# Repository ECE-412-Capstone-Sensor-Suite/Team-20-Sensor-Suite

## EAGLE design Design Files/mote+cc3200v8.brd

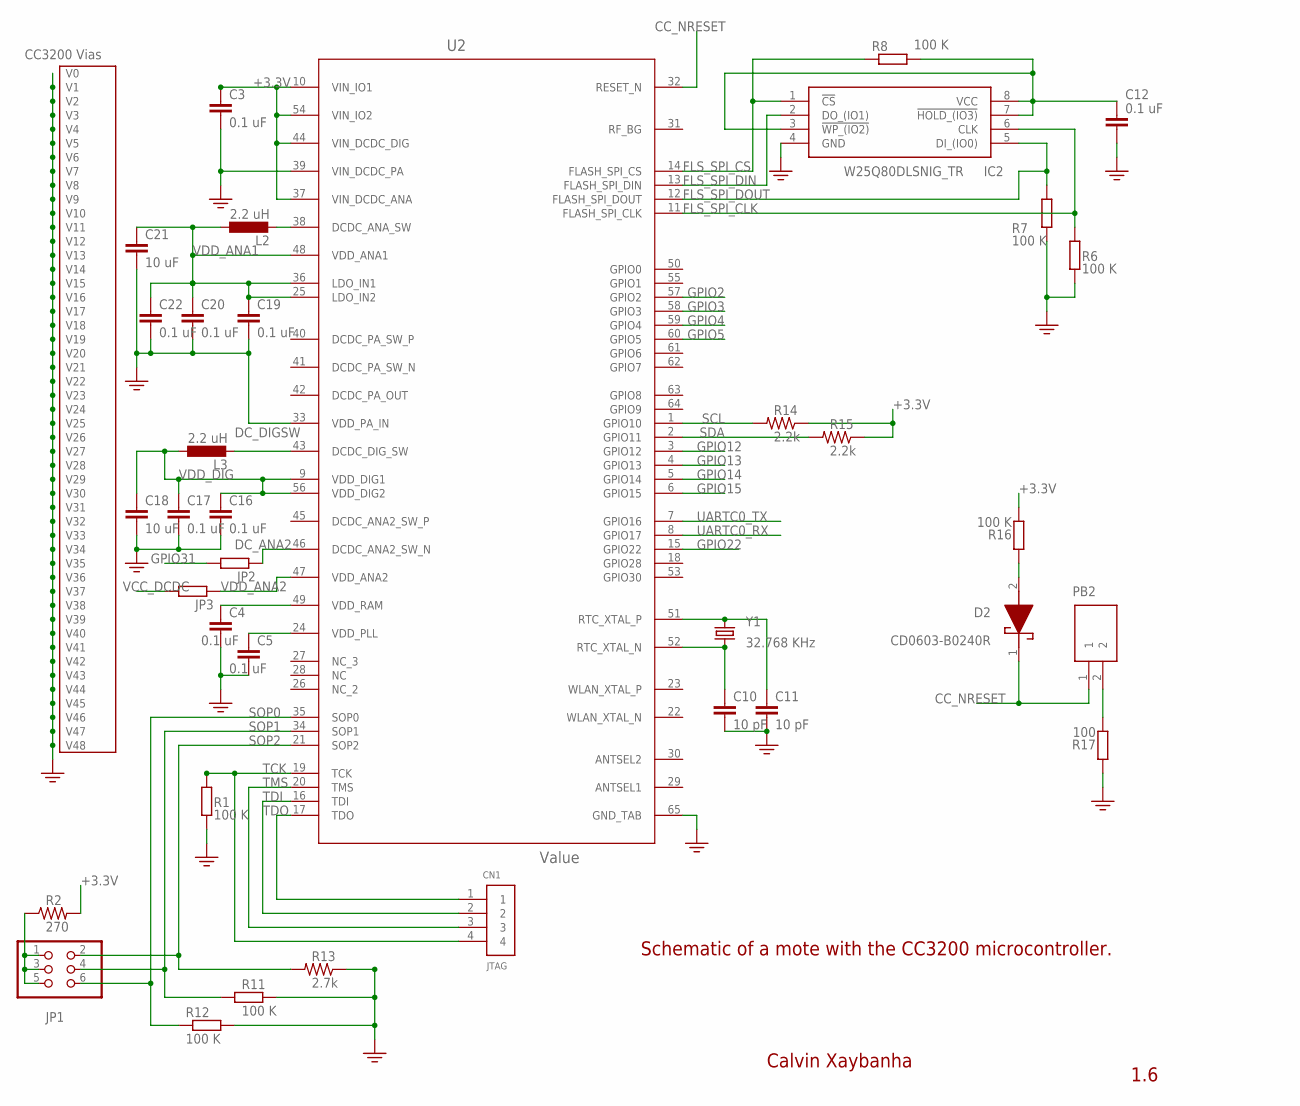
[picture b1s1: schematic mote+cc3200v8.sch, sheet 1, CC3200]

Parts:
C3, C4, C5, C12, C16, C17, C19, C20, C22: 0.1 uF; C1808
C10, C11: 10 pF; C1808
C18, C21: 10 uF; C1808
CN1: JTAG; 1X04-BIG
D2: CD0603-B0240R; CD0603B0240R
IC2: W25Q80DLSNIG_TR; SOIC127P600X175-8N
JP1: PINHD-2X3/90; 2X03/90
JP2, JP3: RR0201; R0201
L2, L3: 2.2 uH; L3216C
PB2: FSMSM
R1, R6, R7, R8, R11, R12, R16: 100 K; R1206
R2: 270; RES_1206
R13: 2.7k; RES_1206
R14, R15: 2.2k; RES_1206
R17: 100; R1206
U2: Value; RGC0064A
Y1: 32.768 KHz; 7.0X5.0

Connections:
+3.3V: C3.1, C12.1, IC2.3 (!WP_(IO2)), IC2.7 (!HOLD_(IO3)), IC2.8 (VCC), R2.2, R8.2, R14.1, R15.1, R16.2, U2.10 (VIN_IO1), U2.37 (VIN_DCDC_ANA), U2.44 (VIN_DCDC_DIG), U2.54 (VIN_IO2); also elsewhere on the board
CC_NRESET: D2.1 (K), PB2.1, U2.32 (RESET_N)
D2_P2: D2.2 (A), R16.1
DCDC_PA_OUT: U2.42 (DCDC_PA_OUT)
DCDC_PA_SW_N: U2.41 (DCDC_PA_SW_N)
DCDC_PA_SW_P: U2.40 (DCDC_PA_SW_P)
DC_ANA2: JP2.1, U2.46 (DCDC_ANA2_SW_N)
DC_DIGSW: L3.2, U2.43 (DCDC_DIG_SW)
FLS_SPI_CLK: IC2.6 (CLK), R6.1, U2.11 (FLASH_SPI_CLK)
FLS_SPI_CS: IC2.1 (!CS), R8.1, U2.14 (FLASH_SPI_CS)
FLS_SPI_DIN: IC2.2 (DO_(IO1)), U2.13 (FLASH_SPI_DIN)
FLS_SPI_DOUT: IC2.5 (DI_(IO0)), R7.1, U2.12 (FLASH_SPI_DOUT)
GND: C3.2, C4.2, C5.2, C10.2, C11.2, C12.2, C16.2, C17.2, C18.2, C19.2, C20.2, C21.2, C22.2, IC2.4 (GND), R1.2, R6.2, R7.2, R11.2, R12.2, R13.1, R17.1, U2.33 (VDD_PA_IN), U2.39 (VIN_DCDC_PA), U2.65 (GND_TAB), U2.V (V0), U2.V_1 (V1), U2.V_2 (V2), U2.V_3 (V3), U2.V_4 (V4), U2.V_5 (V5), U2.V_6 (V6), U2.V_7 (V7), U2.V_8 (V8), U2.V_9 (V9), U2.V_10 (V10), U2.V_11 (V11), U2.V_12 (V12), U2.V_13 (V13), U2.V_14 (V14), U2.V_15 (V15), U2.V_16 (V16), U2.V_17 (V17), U2.V_18 (V18), U2.V_19 (V19), U2.V_20 (V20), U2.V_21 (V21), U2.V_22 (V22), U2.V_23 (V23), U2.V_24 (V24), U2.V_25 (V25), U2.V_26 (V26), U2.V_27 (V27), U2.V_28 (V28), U2.V_29 (V29), U2.V_30 (V30), U2.V_31 (V31), U2.V_32 (V32), U2.V_33 (V33), U2.V_34 (V34), U2.V_35 (V35), U2.V_36 (V36), U2.V_37 (V37), U2.V_38 (V38), U2.V_39 (V39), U2.V_40 (V40), U2.V_41 (V41), U2.V_42 (V42), U2.V_43 (V43), U2.V_44 (V44), U2.V_45 (V45), U2.V_46 (V46), U2.V_47 (V47), U2.V_48 (V48); also elsewhere on the board
GPIO2: U2.57 (GPIO2); also elsewhere on the board
GPIO3: U2.58 (GPIO3); also elsewhere on the board
GPIO4: U2.59 (GPIO4); also elsewhere on the board
GPIO5: U2.60 (GPIO5); also elsewhere on the board
GPIO12: U2.3 (GPIO12); also elsewhere on the board
GPIO13: U2.4 (GPIO13); also elsewhere on the board
GPIO14: U2.5 (GPIO14); also elsewhere on the board
GPIO15: U2.6 (GPIO15); also elsewhere on the board
GPIO22: U2.15 (GPIO22); also elsewhere on the board
GPIO31: JP2.2
JP1_PWR: JP1.1, JP1.3, JP1.5, R2.1
L2_ANA: L2.2, U2.38 (DCDC_ANA_SW)
PB2_2: PB2.2, R17.2
SCL: R14.2, U2.1 (GPIO10); also elsewhere on the board
SDA: R15.2, U2.2 (GPIO11); also elsewhere on the board
SOP0: JP1.6, R12.1, U2.35 (SOP0)
SOP1: JP1.4, R11.1, U2.34 (SOP1)
SOP2: JP1.2, R13.2, U2.21 (SOP2)
TCK: CN1.4, R1.1, U2.19 (TCK)
TDI: CN1.2, U2.16 (TDI)
TDO: CN1.1, U2.17 (TDO)
TMS: CN1.3, U2.20 (TMS)
UARTC0_RX: U2.8 (GPIO17); also elsewhere on the board
UARTC0_TX: U2.7 (GPIO16); also elsewhere on the board
VCC_DCDC: JP3.2
VDD_ANA1: C19.1, C20.1, C21.1, C22.1, L2.1, U2.25 (LDO_IN2), U2.36 (LDO_IN1), U2.48 (VDD_ANA1)
VDD_ANA2: JP3.1, U2.47 (VDD_ANA2)
VDD_DIG: C16.1, C17.1, C18.1, L3.1, U2.9 (VDD_DIG1), U2.56 (VDD_DIG2)
VDD_PULL: C5.1, U2.24 (VDD_PLL)
VDD_RAM: C4.1, U2.49 (VDD_RAM)
XTAL1: C11.1, U2.51 (RTC_XTAL_P), Y1.3 (2)
XTAL2: C10.1, U2.52 (RTC_XTAL_N), Y1.1

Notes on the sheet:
Schematic of a mote with the CC3200 microcontroller.
1.6
Calvin Xaybanha
CC3200 Vias

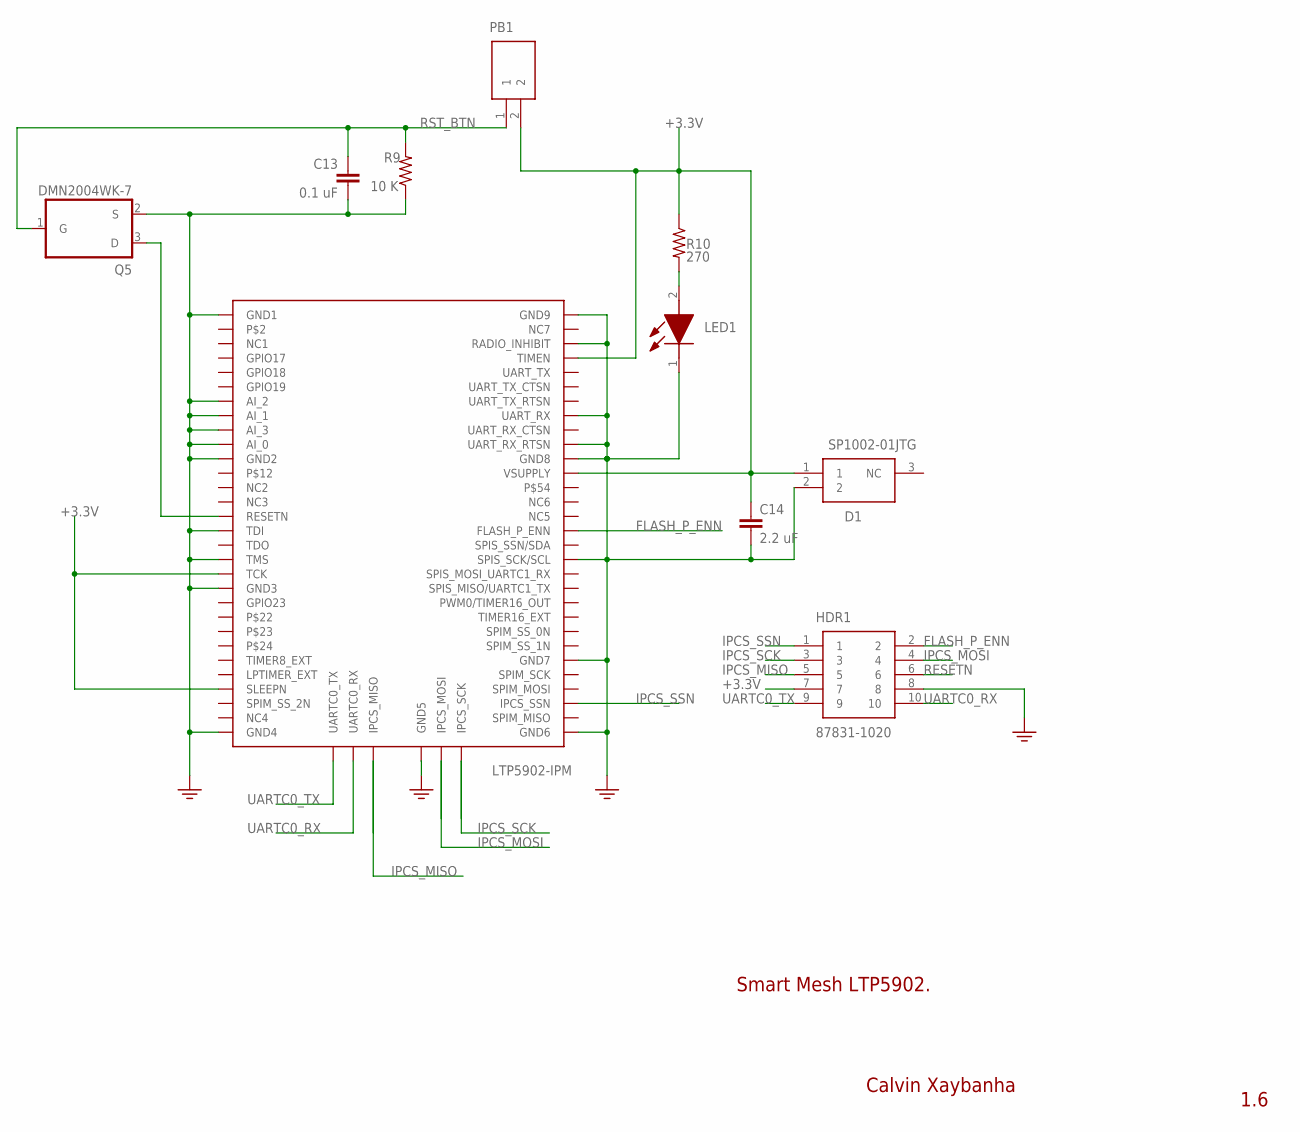
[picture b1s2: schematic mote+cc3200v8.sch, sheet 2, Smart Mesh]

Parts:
C13: 0.1 uF; C1808
C14: 2.2 uF; C1808
D1: SP1002-01JTG; SOT132P220X110-3N
HDR1: 87831-1020; SHDR10W55P200_2X5_1265X630X640
LED1: 156120RS75000; LEDM3216X130N
PB1: FSMSM
Q5: DMN2004WK-7; SC70-3_DCK
R9: 10 K; RES_1206
R10: 270; RES_1206
U3: LTP5902; LTP5902-MMCX

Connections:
+3.3V: C14.1, D1.1, HDR1.7, PB1.2, R10.1, U3.P19 (TCK), U3.P27 (SLEEPN), U3.P55 (VSUPPLY), U3.P63 (TIMEN); also elsewhere on the board
FLASH_P_ENN: HDR1.2, U3.P51 (FLASH_P_ENN)
GND: C13.2, C14.2, D1.2, HDR1.8, LED1.1 (K), Q5.2 (S), R9.1, U3.P1 (GND1), U3.P7 (AI_2), U3.P8 (AI_1), U3.P9 (AI_3), U3.P10 (AI_0), U3.P11 (GND2), U3.P16 (TDI), U3.P18 (TMS), U3.P20 (GND3), U3.P30 (GND4), U3.P34 (GND5), U3.P37 (GND6), U3.P42 (GND7), U3.P49 (SPIS_SCK/SCL), U3.P56 (GND8), U3.P57 (UART_RX_RTSN), U3.P59 (UART_RX), U3.P64 (RADIO_INHIBIT), U3.P66 (GND9); also elsewhere on the board
IPCS_MISO: HDR1.5, U3.P33 (IPCS_MISO)
IPCS_MOSI: HDR1.4, U3.P35 (IPCS_MOSI)
IPCS_SCK: HDR1.3, U3.P36 (IPCS_SCK)
IPCS_SSN: HDR1.1, U3.P39 (IPCS_SSN)
LED1: LED1.2 (A), R10.2
RESETN: HDR1.6, Q5.3 (D), U3.P15 (RESETN)
RST_BTN: C13.1, PB1.1, Q5.1 (G), R9.2
UARTC0_RX: HDR1.10, U3.P32 (UARTC0_RX); also elsewhere on the board
UARTC0_TX: HDR1.9, U3.P31 (UARTC0_TX); also elsewhere on the board

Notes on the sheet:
Calvin Xaybanha
1.6
Smart Mesh LTP5902.
LTP5902-IPM

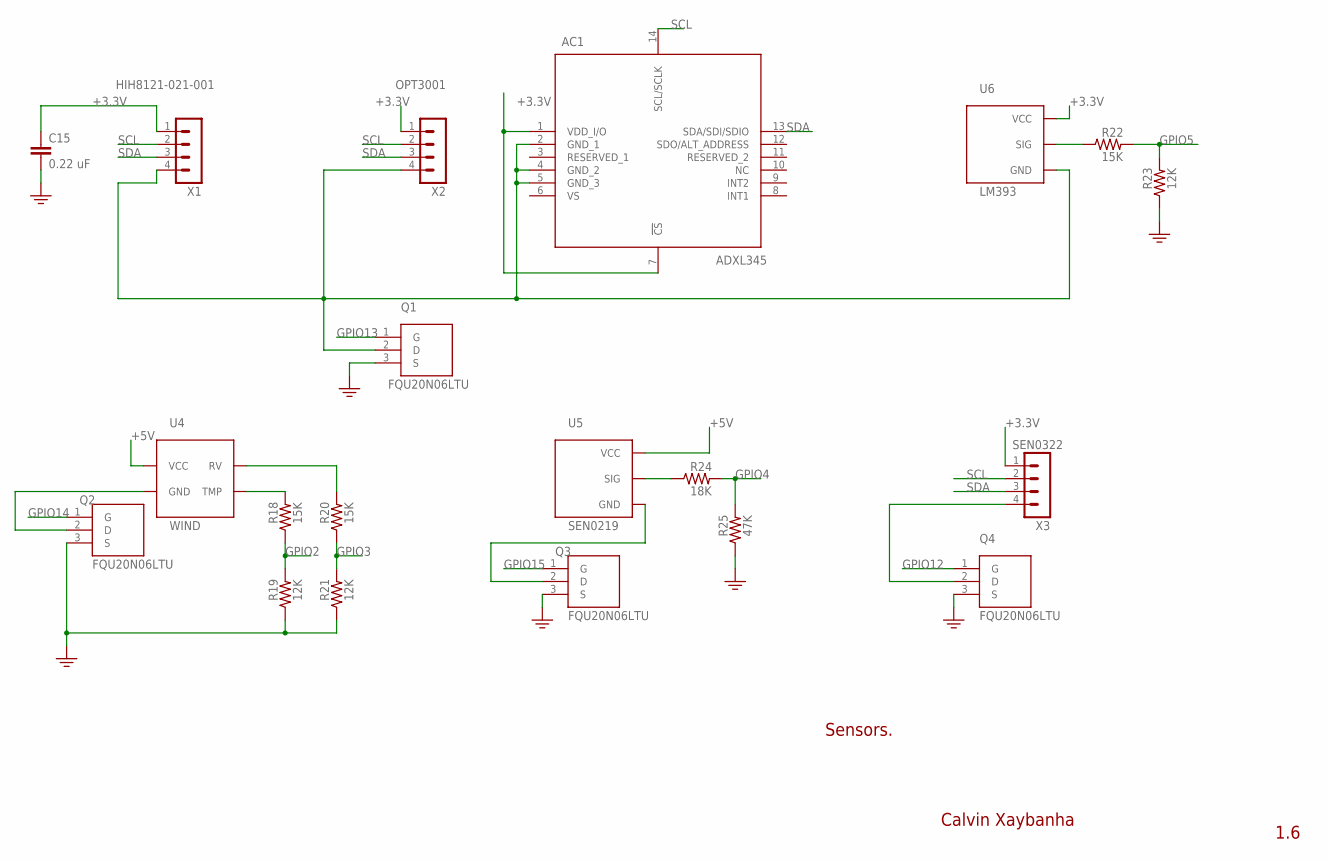
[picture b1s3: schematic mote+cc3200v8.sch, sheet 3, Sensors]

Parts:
AC1: ADXL345; CC-14-1
C15: 0.22 uF; C1808
Q1, Q2, Q3, Q4: FQU20N06LTU; TO229P250X658X985-3P
R18, R20, R22: 15K; RES_1206
R19, R21, R23: 12K; RES_1206
R24: 18K; RES_1206
R25: 47K; RES_1206
U4: WIND
U5: SEN0219
U6: LM393
X1: HIH8121-021-001; B4B-PH-K-S
X2: OPT3001; B4B-PH-K-S
X3: SEN0322; B4B-PH-K-S

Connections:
+3.3V: AC1.1 (VDD_I/O), AC1.7 (!CS), C15.1, U6.P$1 (VCC), X1.1, X2.1, X3.1; also elsewhere on the board
+5V: U4.P$1 (VCC), U5.P$1 (VCC); also elsewhere on the board
GND: C15.2, Q1.3 (S), Q2.3 (S), Q3.3 (S), Q4.3 (S), R19.1, R21.1, R23.1, R25.1; also elsewhere on the board
GPIO2: R18.1, R19.2; also elsewhere on the board
GPIO3: R20.1, R21.2; also elsewhere on the board
GPIO4: R24.2, R25.2; also elsewhere on the board
GPIO5: R22.2, R23.2; also elsewhere on the board
GPIO12: Q4.1 (G); also elsewhere on the board
GPIO13: Q1.1 (G); also elsewhere on the board
GPIO14: Q2.1 (G); also elsewhere on the board
GPIO15: Q3.1 (G); also elsewhere on the board
Q1+: AC1.2 (GND_1), AC1.4 (GND_2), AC1.5 (GND_3), Q1.2 (D), U6.P$3 (GND), X1.4, X2.4
Q2+: Q2.2 (D), U4.P$2 (GND)
Q3+: Q3.2 (D), U5.P$3 (GND)
Q4+: Q4.2 (D), X3.4
R18_1: R18.2, U4.P$4 (TMP)
R20_1: R20.2, U4.P$3 (RV)
R22_1: R22.1, U6.P$2 (SIG)
R24_1: R24.1, U5.P$2 (SIG)
SCL: AC1.14 (SCL/SCLK), X1.2, X2.2, X3.2; also elsewhere on the board
SDA: AC1.13 (SDA/SDI/SDIO), X1.3, X2.3, X3.3; also elsewhere on the board

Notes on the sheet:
Calvin Xaybanha
1.6
Sensors.

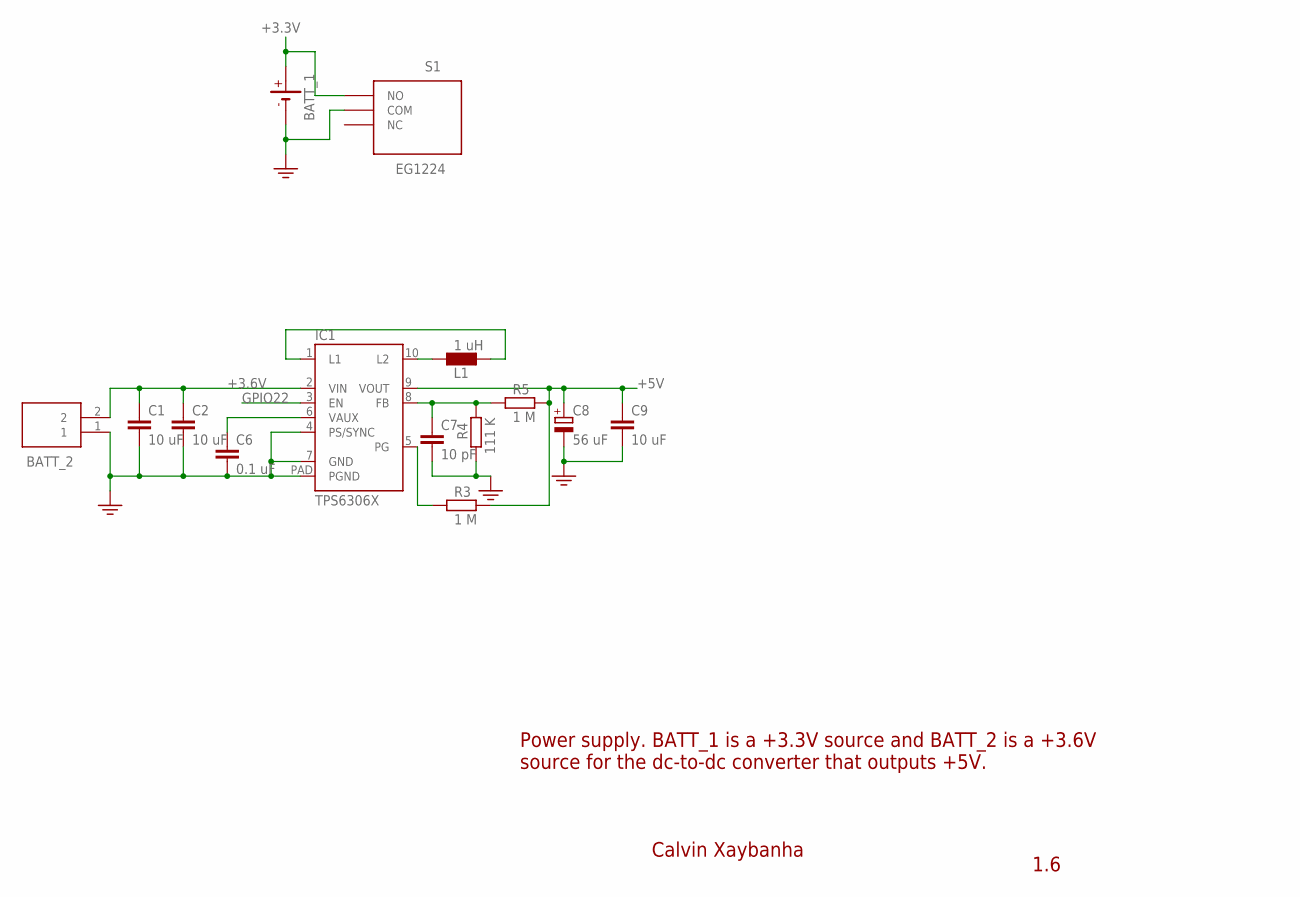
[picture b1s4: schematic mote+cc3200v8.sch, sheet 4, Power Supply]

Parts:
BATT_1: BATTERY_BR1225/FA
BATT_2: 12BH23P-GR; 12BH23PGR
C1, C2, C9: 10 uF; C1808
C6: 0.1 uF; C1808
C7: 10 pF; C1808
C8: 56 uF; E3,5-8
IC1: TPS6306X; S-PWSON-N10
L1: 1 uH; 0204/7
R3, R5: 1 M; R5025
R4: 111 K; R1206
S1: EG1224

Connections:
+3.3V: BATT_1.+, S1.1 (NO); also elsewhere on the board
+3.6V: BATT_2.2, C1.1, C2.1, IC1.2 (VIN)
+5V: C8.+, C9.1, IC1.9 (VOUT), R3.2, R5.2; also elsewhere on the board
FB_TPS: C7.1, IC1.8 (FB), R4.2, R5.1
GND: BATT_1.-, BATT_2.1, C1.2, C2.2, C6.2, C7.2, C8.-, C9.2, IC1.4 (PS/SYNC), IC1.7 (GND), IC1.PAD (PGND), R4.1, S1.2 (COM); also elsewhere on the board
GPIO22: IC1.3 (EN); also elsewhere on the board
L_TPS1: IC1.1 (L1), L1.2
L_TPS2: IC1.10 (L2), L1.1
PG_TPS: IC1.5 (PG), R3.1
VAUX_TPS: C6.1, IC1.6 (VAUX)

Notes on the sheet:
Calvin Xaybanha
1.6
Power supply. BATT_1 is a +3.3V source and BATT_2 is a +3.6V source for the dc-to-dc converter that outputs +5V.

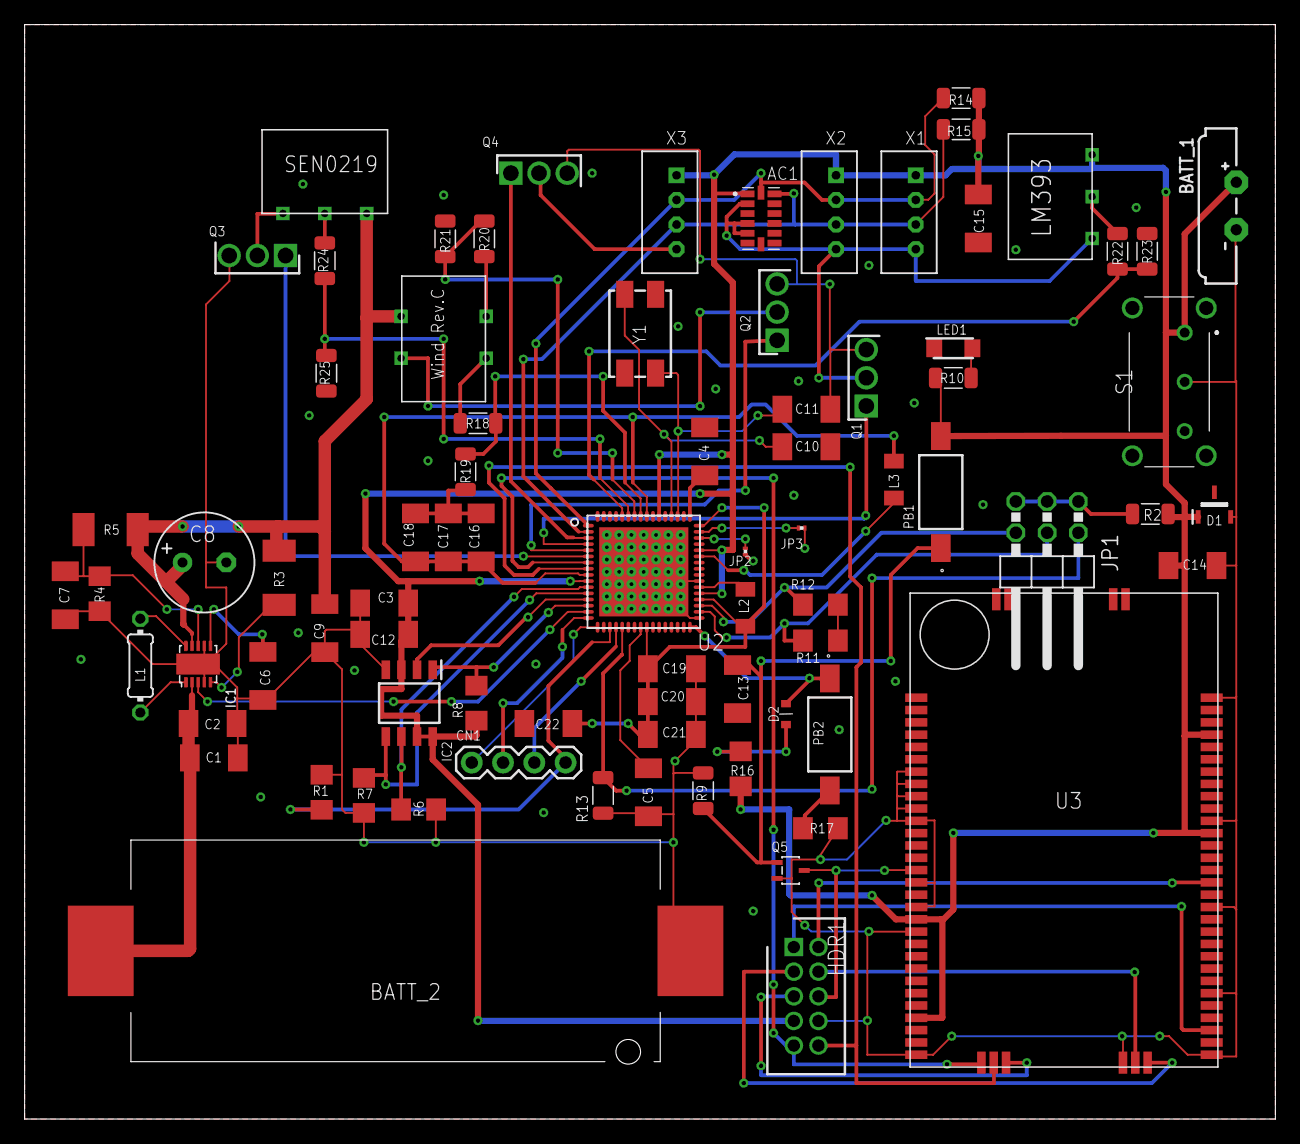
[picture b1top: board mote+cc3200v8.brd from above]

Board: 2 copper layers, 101.6 x 88.9 mm, 80 parts (0 on the bottom side), 63 nets.

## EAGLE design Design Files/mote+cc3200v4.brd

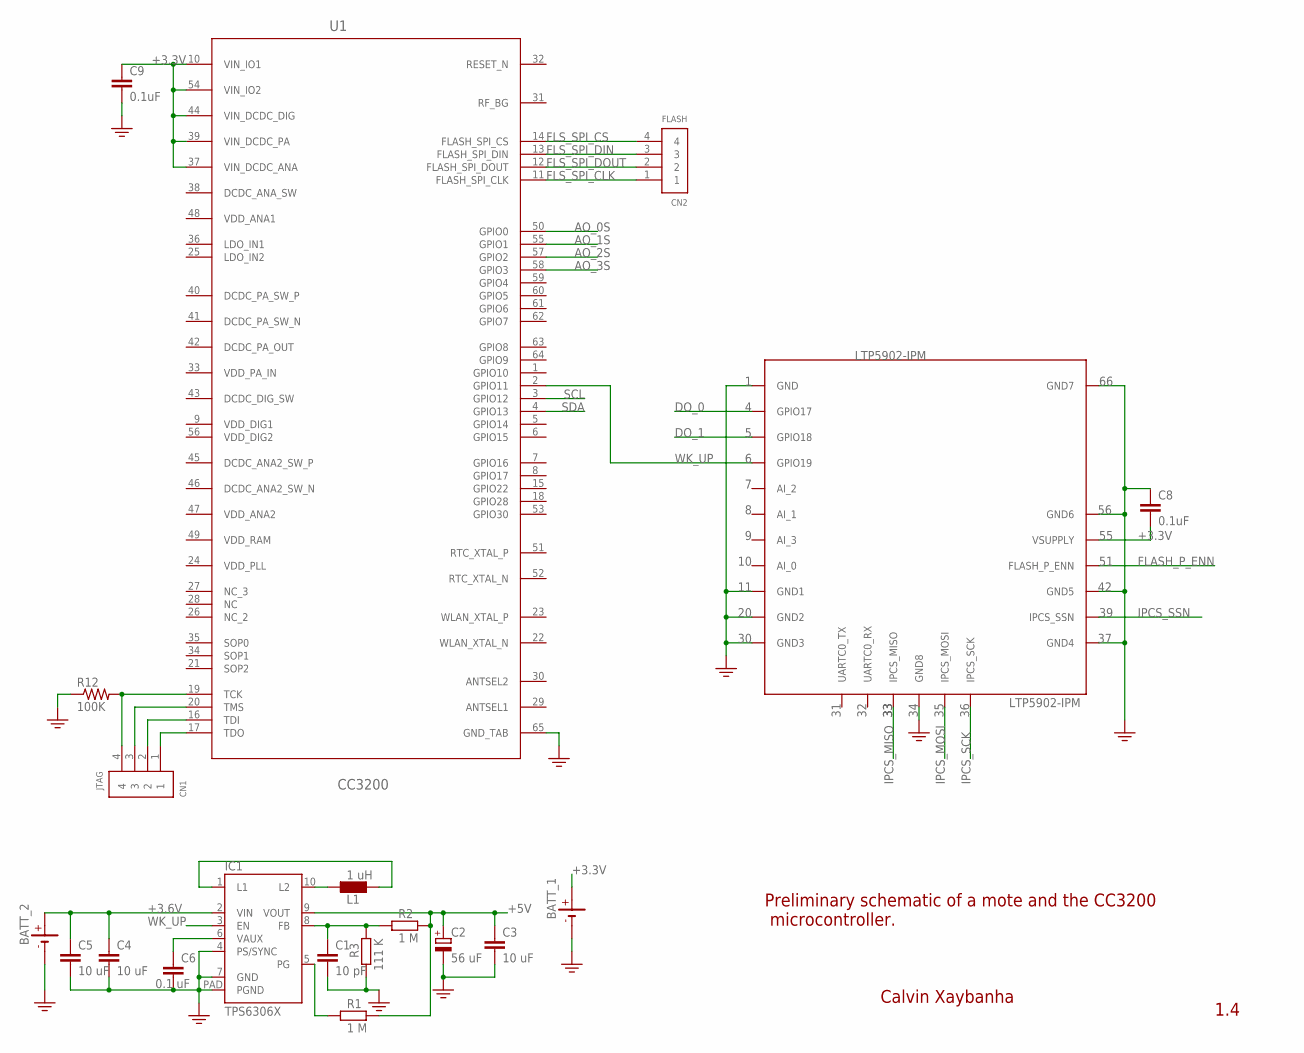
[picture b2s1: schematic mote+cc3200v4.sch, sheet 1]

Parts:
BATT_1, BATT_2: BATTERY_BR1225/FA
C1: 10 pF; C1808
C2: 56 uF; E3,5-8
C3, C4, C5: 10 uF; C1808
C6: 0.1 uF; C1808
C8, C9: 0.1uF; C5B3.5
CN1: JTAG; 1X04-BIG
CN2: FLASH; 1X04-BIG
IC1: TPS6306X; S-PWSON-N10
L1: 1 uH; 0204/7
R1, R2: 1 M; R5025
R3: 111 K; R1206
R12: 100K; 0207/10
U1: CC3200; RGC0064A
U5: LTP5902; LTP5901

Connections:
3.3V: U5.P$1 (GND), U5.P$9 (GND1), U5.P$10 (GND2), U5.P$11 (GND3); also elsewhere on the board
+3.3V: BATT_1.+, C8.2, C9.1, U1.10 (VIN_IO1), U1.37 (VIN_DCDC_ANA), U1.39 (VIN_DCDC_PA), U1.44 (VIN_DCDC_DIG), U1.54 (VIN_IO2), U5.P$22 (VSUPPLY); also elsewhere on the board
+3.6V: BATT_2.+, C4.1, C5.1, IC1.2 (VIN)
+5V: C2.+, C3.1, IC1.9 (VOUT), R1.2, R2.2; also elsewhere on the board
AO_0S: U1.50 (GPIO0)
AO_1S: U1.55 (GPIO1); also elsewhere on the board
AO_2S: U1.57 (GPIO2); also elsewhere on the board
AO_3S: U1.58 (GPIO3); also elsewhere on the board
DCDC_ANA_SW: U1.38 (DCDC_ANA_SW)
DCDC_DIG_SW: U1.43 (DCDC_DIG_SW)
DCDC_PA_OUT: U1.42 (DCDC_PA_OUT)
DCDC_PA_SW_N: U1.41 (DCDC_PA_SW_N)
DCDC_PA_SW_P: U1.40 (DCDC_PA_SW_P)
DO_0: U5.P$2 (GPIO17)
DO_1: U5.P$3 (GPIO18)
FB_TPS: C1.1, IC1.8 (FB), R2.1, R3.2
FLASH_P_ENN: U5.P$21 (FLASH_P_ENN)
FLS_SPI_CLK: CN2.1, U1.11 (FLASH_SPI_CLK)
FLS_SPI_CS: CN2.4, U1.14 (FLASH_SPI_CS)
FLS_SPI_DIN: CN2.3, U1.13 (FLASH_SPI_DIN)
FLS_SPI_DOUT: CN2.2, U1.12 (FLASH_SPI_DOUT)
GND: BATT_1.-, BATT_2.-, C1.2, C2.-, C3.2, C4.2, C5.2, C6.2, C8.1, C9.2, IC1.4 (PS/SYNC), IC1.7 (GND), IC1.PAD (PGND), R3.1, R12.1, U1.65 (GND_TAB), U5.P$15 (GND8), U5.P$18 (GND4), U5.P$20 (GND5), U5.P$23 (GND6), U5.P$24 (GND7); also elsewhere on the board
IPCS_MISO: U5.P$14 (IPCS_MISO)
IPCS_MOSI: U5.P$16 (IPCS_MOSI)
IPCS_SCK: U5.P$17 (IPCS_SCK)
IPCS_SSN: U5.P$19 (IPCS_SSN)
LDO_IN1: U1.36 (LDO_IN1)
LDO_IN2: U1.25 (LDO_IN2)
L_TPS1: IC1.1 (L1), L1.2
L_TPS2: IC1.10 (L2), L1.1
unnamed: CN1.4, R12.2, U1.19 (TCK)
unnamed: CN1.3, U1.20 (TMS)
unnamed: CN1.2, U1.16 (TDI)
unnamed: CN1.1, U1.17 (TDO)
PG_TPS: IC1.5 (PG), R1.1
SCL: U1.3 (GPIO12); also elsewhere on the board
SDA: U1.4 (GPIO13); also elsewhere on the board
VAUX_TPS: C6.1, IC1.6 (VAUX)
VDD_ANA1: U1.48 (VDD_ANA1)
VDD_ANA2: U1.47 (VDD_ANA2)
VDD_DIG1: U1.9 (VDD_DIG1)
VDD_DIG2: U1.56 (VDD_DIG2)
VDD_PA_IN: U1.33 (VDD_PA_IN)
VDD_PLL: U1.24 (VDD_PLL)
VDD_RAM: U1.49 (VDD_RAM)
WK_UP: IC1.3 (EN), U1.2 (GPIO11), U5.P$4 (GPIO19)

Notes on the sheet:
Preliminary schematic of a mote and the CC3200 microcontroller.
1.4
Calvin Xaybanha
LTP5902-IPM

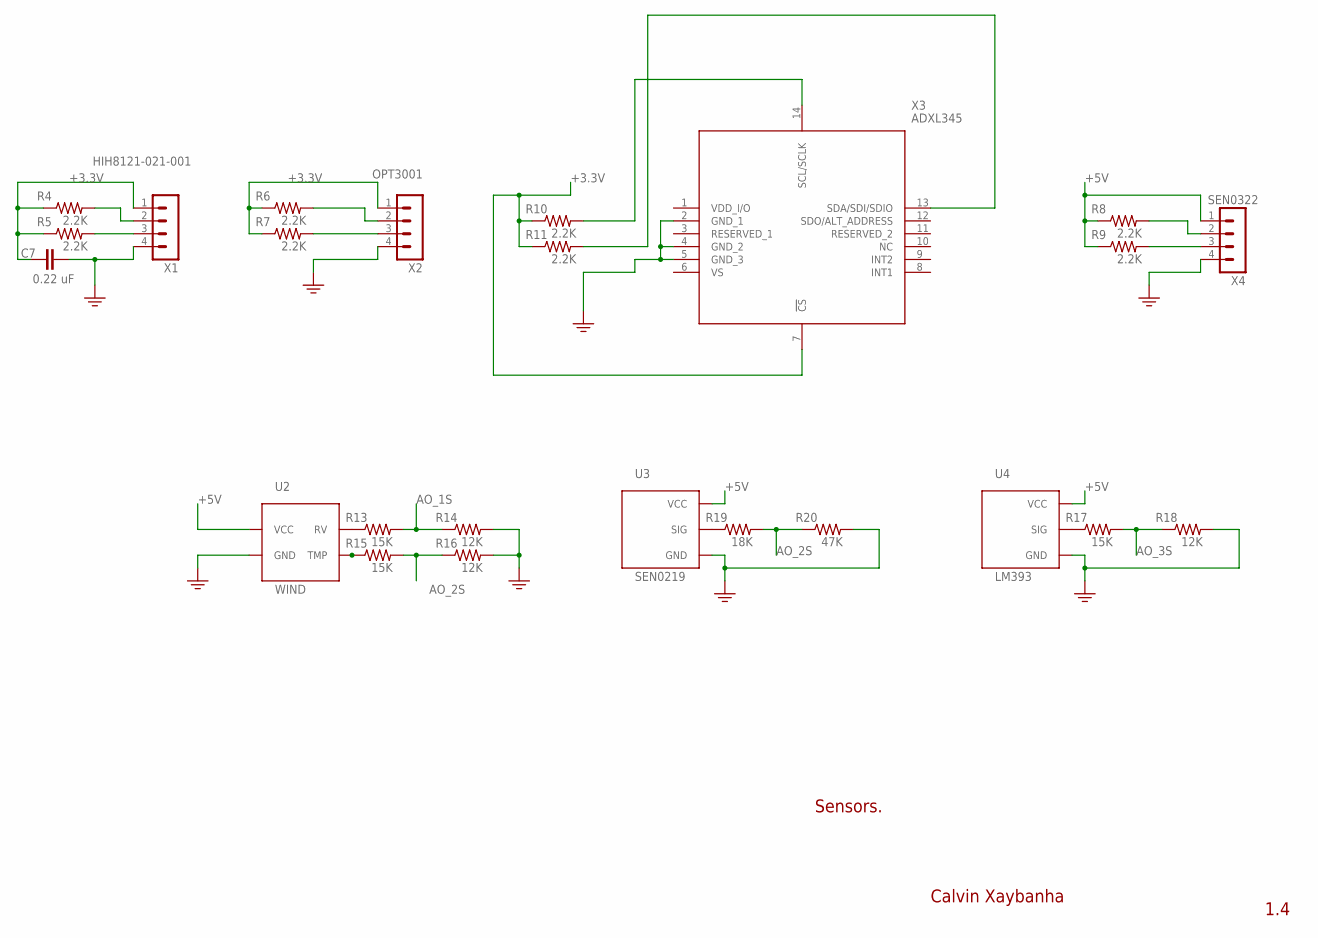
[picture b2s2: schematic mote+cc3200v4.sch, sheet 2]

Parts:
C7: 0.22 uF; C5B3.5
R4, R5, R6, R7, R8, R9, R10, R11: 2.2K; 0207/9
R13, R15, R17: 15K; 0207/9
R14, R16, R18: 12K; 0207/9
R19: 18K; 0207/9
R20: 47K; 0207/9
U2: WIND
U3: SEN0219
U4: LM393
X1: HIH8121-021-001; B4B-PH-K-S
X2: OPT3001; B4B-PH-K-S
X3: ADXL345; CC-14-1
X4: SEN0322; B4B-PH-K-S

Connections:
3.3V: R14.2, R16.2; also elsewhere on the board
+3.3V: C7.1, R4.1, R5.1, R6.1, R7.1, R10.1, R11.1, X1.1, X2.1, X3.7 (!CS); also elsewhere on the board
+5V: R8.1, R9.1, U2.P$1 (VCC), U3.P$1 (VCC), U4.P$1 (VCC), X4.1; also elsewhere on the board
AO_1S: R13.2, R14.1; also elsewhere on the board
AO_2S: R15.2, R16.1, R19.2, R20.1; also elsewhere on the board
AO_3S: R17.2, R18.1; also elsewhere on the board
GND: C7.2, R18.2, R20.2, U2.P$2 (GND), U3.P$3 (GND), U4.P$3 (GND), X1.4, X2.4, X3.2 (GND_1), X3.4 (GND_2), X3.5 (GND_3), X4.4; also elsewhere on the board
unnamed: R7.2, X2.3
unnamed: R11.2, X3.13 (SDA/SDI/SDIO)
unnamed: R13.1, U2.P$3 (RV)
unnamed: R17.1, U4.P$2 (SIG)
unnamed: R15.1, U2.P$4 (TMP)
unnamed: R19.1, U3.P$2 (SIG)
SCL: R4.2, R6.2, R8.2, R10.2, X1.2, X2.2, X3.14 (SCL/SCLK), X4.2; also elsewhere on the board
SDA: R5.2, R9.2, X1.3, X4.3; also elsewhere on the board
VDD_I/O: X3.1 (VDD_I/O)

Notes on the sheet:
Calvin Xaybanha
1.4
Sensors.

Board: 2 copper layers, 44 parts (0 on the bottom side), 30 nets, no tracks yet.

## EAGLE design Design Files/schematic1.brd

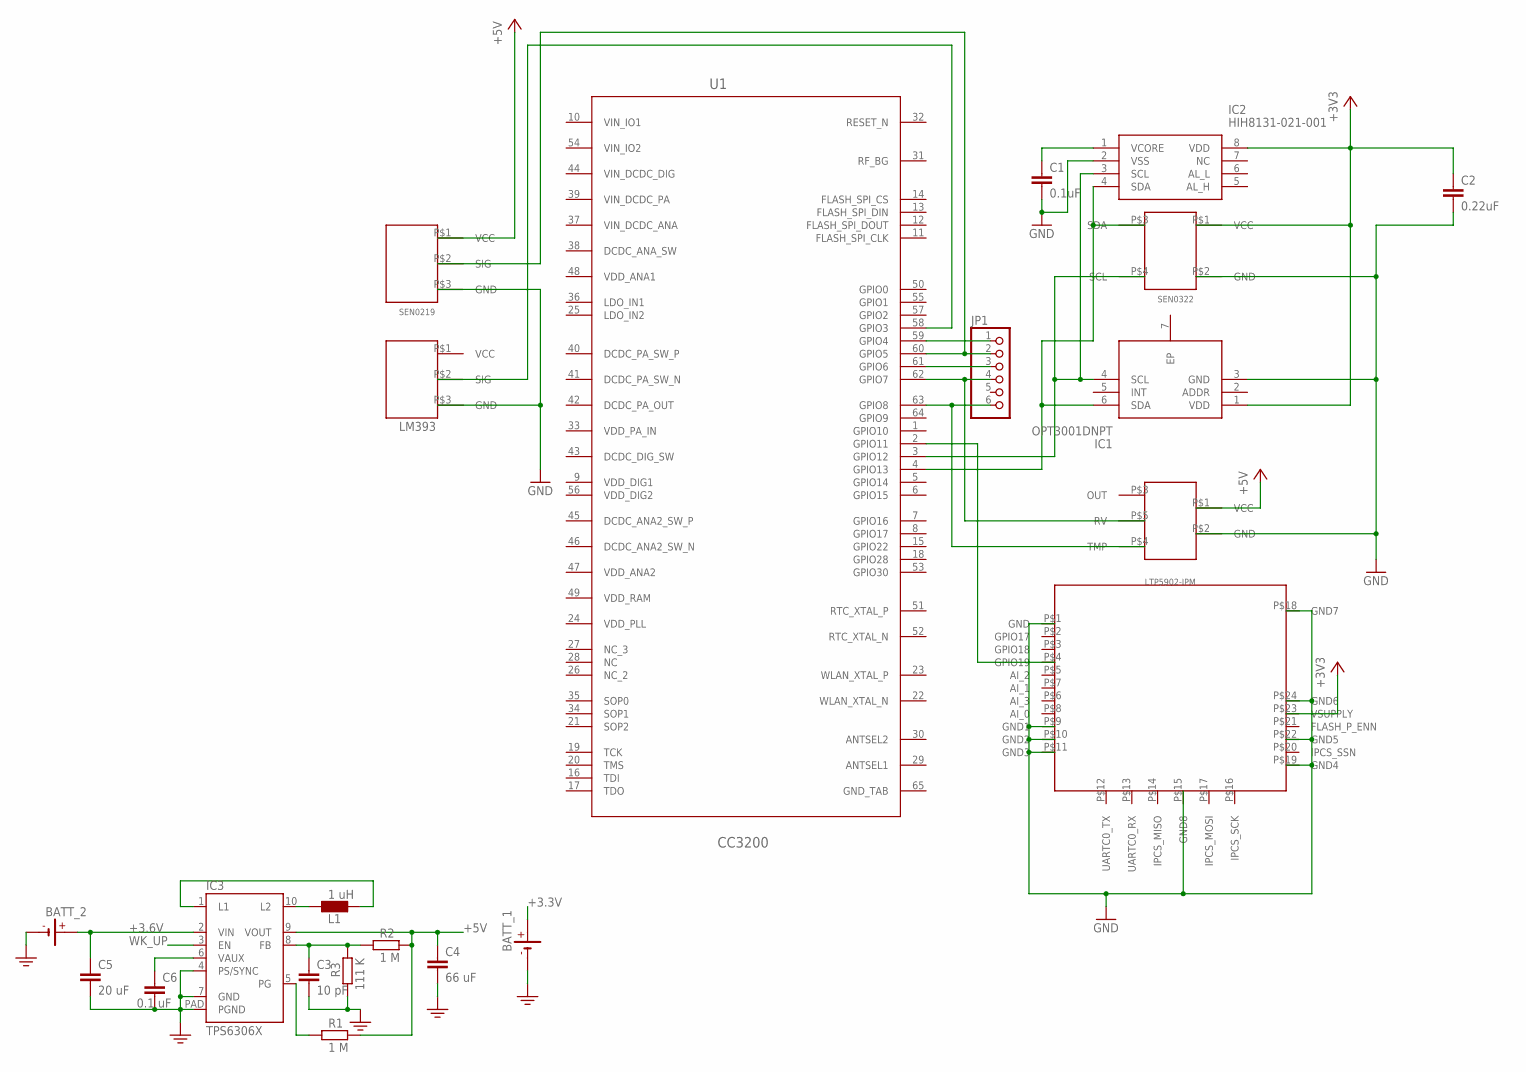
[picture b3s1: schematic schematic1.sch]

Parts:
BATT_1, BATT_2: BATTERY_BR1225/FA
C1: 0.1uF; C2.5-2
C2: 0.22uF; C2.5-2
C3: 10 pF; C1808
C4: 66 uF; C1808
C5: 20 uF; C1808
C6: 0.1 uF; C1808
IC1: OPT3001DNPT; SON65P200X200X65-7N
IC2: HIH8131-021-001; SOIC127P600X206-8N
IC3: TPS6306X; S-PWSON-N10
JP1: PINHD-1X6CB; 1X06-CLEANBIG
L1: 1 uH; 0204/7
R1, R2: 1 M; R2010
R3: 111 K; R2010
U1: CC3200; RGC0064A
U2: WIND
U3: SEN0322
U4: SEN0219
U5: LM393
U6: LTP5902; LTP5901

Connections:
+3.3V: BATT_1.+
+3.6V: BATT_2.+, C5.1, IC3.2 (VIN)
+3V3: C2.1, IC1.1 (VDD), IC2.8 (VDD), U3.P$1 (VCC), U6.P$23 (VSUPPLY)
+5V: C4.1, IC3.9 (VOUT), R1.2, R2.2, U2.P$1 (VCC), U4.P$1 (VCC)
DCDC_ANA_SW: U1.38 (DCDC_ANA_SW)
DCDC_DIG_SW: U1.43 (DCDC_DIG_SW)
DCDC_PA_OUT: U1.42 (DCDC_PA_OUT)
DCDC_PA_SW_N: U1.41 (DCDC_PA_SW_N)
DCDC_PA_SW_P: U1.40 (DCDC_PA_SW_P)
FB_TPS: C3.1, IC3.8 (FB), R2.1, R3.2
GND: BATT_1.-, BATT_2.-, C1.2, C2.2, C3.2, C4.2, C5.2, C6.2, IC1.3 (GND), IC2.2 (VSS), IC3.4 (PS/SYNC), IC3.7 (GND), IC3.PAD (PGND), R3.1, U2.P$2 (GND), U3.P$2 (GND), U4.P$3 (GND), U5.P$3 (GND), U6.P$1 (GND), U6.P$9 (GND1), U6.P$10 (GND2), U6.P$11 (GND3), U6.P$15 (GND8), U6.P$18 (GND7), U6.P$19 (GND4), U6.P$22 (GND5), U6.P$24 (GND6)
GND_TAB: U1.65 (GND_TAB)
LDO_IN1: U1.36 (LDO_IN1)
LDO_IN2: U1.25 (LDO_IN2)
L_TPS1: IC3.1 (L1), L1.2
L_TPS2: IC3.10 (L2), L1.1
unnamed: JP1.1, U1.59 (GPIO4)
unnamed: JP1.2, U1.60 (GPIO5), U4.P$2 (SIG)
unnamed: U1.2 (GPIO11), U6.P$4 (GPIO19)
unnamed: U1.58 (GPIO3), U5.P$2 (SIG)
unnamed: JP1.3, U1.61 (GPIO6)
unnamed: JP1.4, U1.62 (GPIO7), U2.P$5 (RV)
unnamed: JP1.6, U1.63 (GPIO8), U2.P$4 (TMP)
unnamed: C1.1, IC2.1 (VCORE)
unnamed: IC1.4 (SCL), IC2.3 (SCL), U1.3 (GPIO12), U3.P$4 (SCL)
unnamed: IC1.6 (SDA), IC2.4 (SDA), U1.4 (GPIO13), U3.P$3 (SDA)
PG_TPS: IC3.5 (PG), R1.1
VAUX_TPS: C6.1, IC3.6 (VAUX)
VDD_ANA1: U1.48 (VDD_ANA1)
VDD_ANA2: U1.47 (VDD_ANA2)
VDD_DIG1: U1.9 (VDD_DIG1)
VDD_DIG2: U1.56 (VDD_DIG2)
VDD_PA_IN: U1.33 (VDD_PA_IN)
VDD_PLL: U1.24 (VDD_PLL)
VDD_RAM: U1.49 (VDD_RAM)
VIN_DCDC_ANA: U1.37 (VIN_DCDC_ANA)
VIN_DCDC_DIG: U1.44 (VIN_DCDC_DIG)
VIN_DCDC_PA: U1.39 (VIN_DCDC_PA)
VIN_IO1: U1.10 (VIN_IO1)
VIN_IO2: U1.54 (VIN_IO2)
WK_UP: IC3.3 (EN)

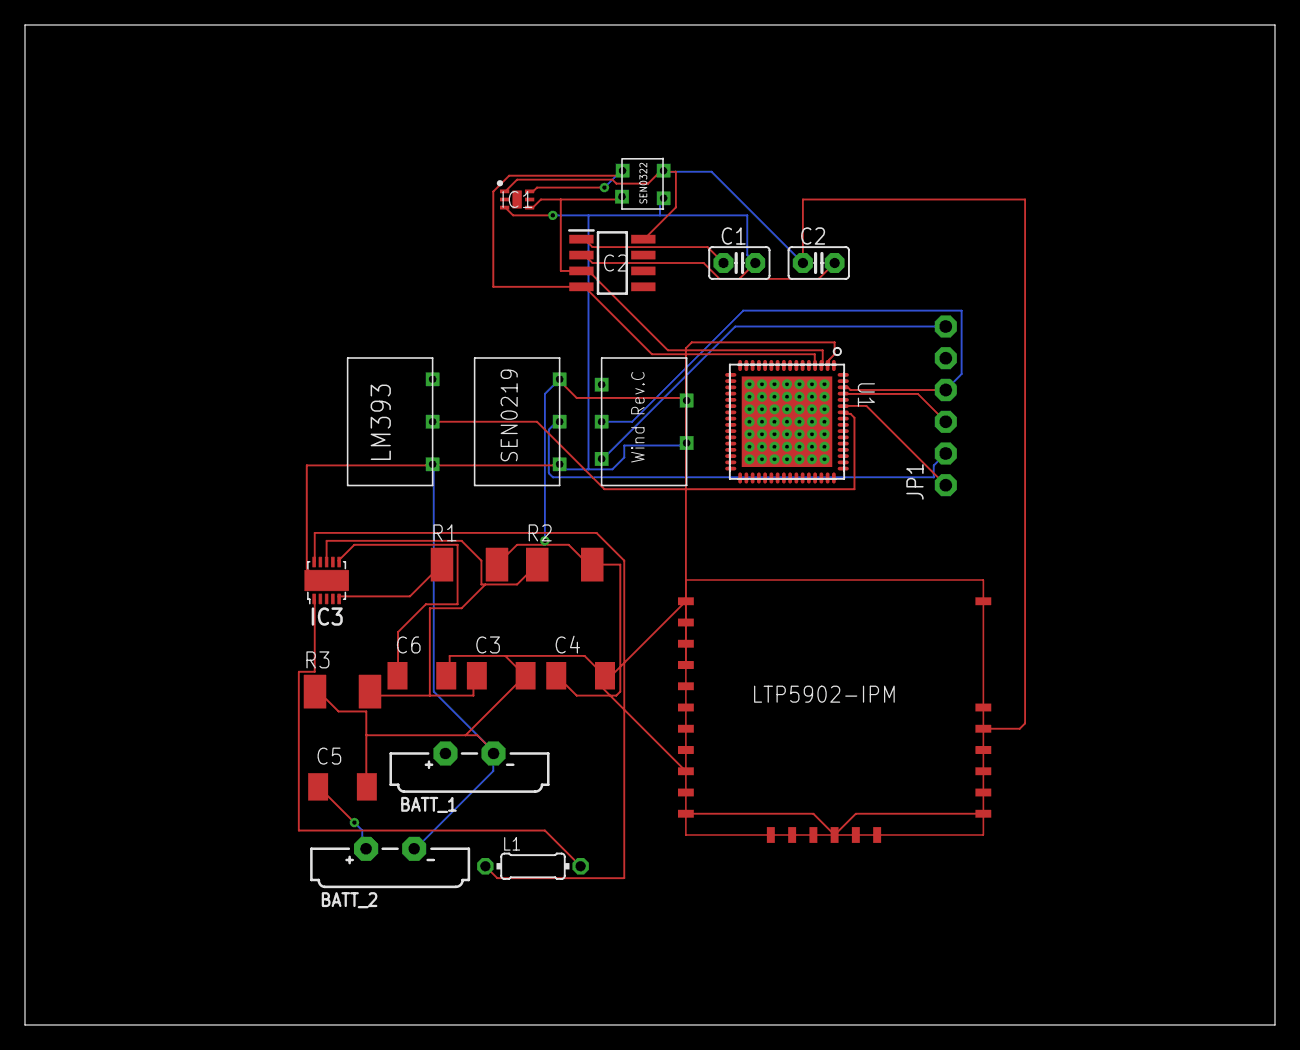
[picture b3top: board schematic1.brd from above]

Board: 2 copper layers, 100.0 x 80.0 mm, 22 parts (0 on the bottom side), 19 nets.

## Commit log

2021-02-06 Create About
2021-02-19 Create name
2021-02-19 Add files via upload
    Version 1.0
2021-02-19 Version 1.0
2021-02-27 Update I2C_CHAIN.ino
    update I2C Chain code!!
2021-02-28 node red exploration
2021-03-04 Smart mesh Python scripts and libraries
2021-03-04 OAP logger to log sensor data onto log file
2021-03-04 OAP logger.md
    This is where we connect to the manager and receive and organize sensor data sent for the OAP(on-chip application) that we loaded onto the motes.
2021-03-04 Adding all required libraries to being on chip programing
2021-03-05 organized Onchip library
2021-03-05 Create insert
2021-03-05 Create DFRobot O2 Library
2021-03-05 Create code
2021-03-06 Create code1
2021-03-06 I2C_ChainV2 upgraded
2021-03-06 replacing o2 library sextion with i2C Chain O2 fxn
2021-03-11 On chip SDK update
2021-03-12 MESH NETWORK DATA structure, USE TESTING.py to see how structure works
2021-03-13 Python class structure
2021-04-16 adding Smart mesh C-library
2021-04-16 UPDATING I2C CHAIN ENERGIA WITH SMART MESH CODE
2021-04-16 Data Visualization_Presentation
2021-04-16 Data visualization
2021-04-16 Create Data visialization
2021-04-16 Adding libraries needed for Smartmesh integration into I2C chain
2021-04-21 Library required to run V5 firmware
2021-04-21 Firmware for CC3200
2021-04-21 Add files via upload
    have comments
2021-05-01 Reorganizing and updating Engergia code
2021-05-01 organizing
2021-05-01 Adding sensor data sending bia SmartMesh
2021-05-01 Added Design Files Folder
    Schematic, board, and pdf file of schematic added.
2021-05-03 Fixing send value crash bug
2021-05-03 Add files via upload
    PCB design Version2
2021-05-03 Create lbr file
2021-05-03 Create a
2021-05-04 MAIN DEPLOYABLE SENSOR MOTE CODE FOR CC3200
2021-05-05 fixed bug
2021-05-06 adding red led
2021-05-13 Sensor logger and sensor mote V1.1
2021-05-15 adding V1.2
2021-05-16 Updated Design Files and Libraries
    Some libraries included in the design were added.
2021-05-18 New logging formate and logging software
2021-05-20 made script changes
2021-05-22 new GUI
2021-05-24 Updated design files.
    Overwritten original mote+cc3200 files to revision 1.5. Added CAM data files in zip folder for PCB fabrication.
2021-05-25 Design files revised.
    Added SOP connections to the design.
    Ground stitched vias on the board were placed.
2021-05-28 Version 6 of Design
    -Updated board to be 4"x3.5".
    -Changed Isolation from 1 to 16 for ground layers.
    -Generated updated CAM files.
    -Fixed connections to Smart Mesh Headers.
    -Separated the schematic into 4 pages.
    -Added more schematic modules for organization.
2021-06-02 adding sensor suite GUI
2021-06-03 Final GUI version
2021-06-03 updating logger
2021-06-03 scalled GUI down
2021-06-03 Version 7 of the Schematic and Board
    -Revised according to schematic review on 5/28/2021.
    -Added reset button for CC3200.
    -Tied some power and input pins to ground on both controllers.
2021-06-03 updating GUI
2021-06-03 tkinter optimization
2021-06-03 gui optimizations
2021-06-03 adding comments to code
2021-06-10 API update
2021-06-10 Mote schematic/PCB Updated
    Analog sensors were given voltage dividers at 1.4V scale to be within the CC3200's ADC range.
2021-06-11 Rearranging Github
2021-06-11 adding operation guide

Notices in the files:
parts and their libraries:
SparkFun-PowerSymbols: Licensing: Creative Commons ShareAlike 4.0 International - https://creativecommons.org/licenses/by-sa/4.0
crystal-geyer_V1_0: Copyright: Geyer-Electronic
